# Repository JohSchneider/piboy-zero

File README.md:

# Pi-Boy Zero
aka "PiGrrl-Zero"

[hackaday.io project](https://hackaday.io/project/9467-pigrrl-zero)

*yet another portable console! ;-)*

roughly the size of a gameboy micro, with a 2.2" display

this repository holds:
- the pcb-schematics (kicad)
- stl files for a 3d printable case
- and various setup scripts/tools/config-files to get emulationstation running on this particular hardware setup

## the progress so far

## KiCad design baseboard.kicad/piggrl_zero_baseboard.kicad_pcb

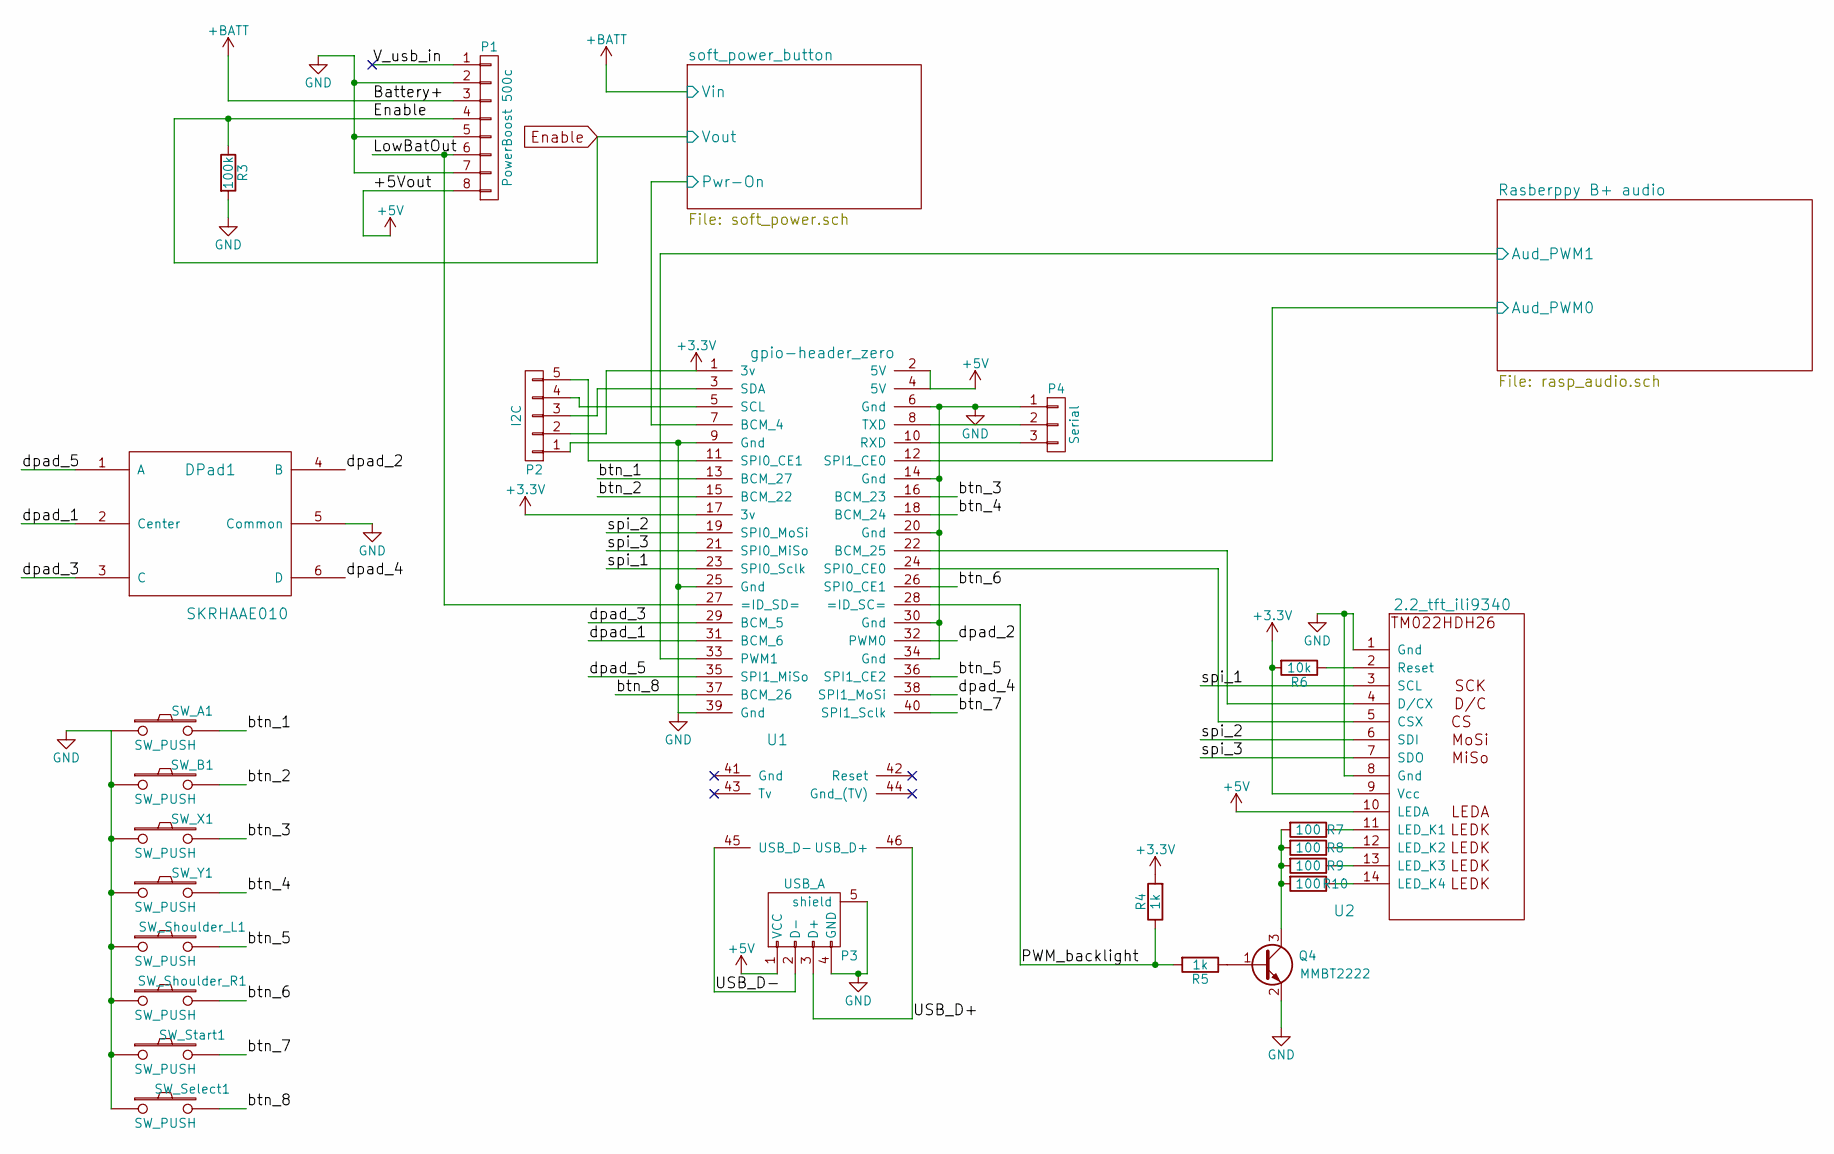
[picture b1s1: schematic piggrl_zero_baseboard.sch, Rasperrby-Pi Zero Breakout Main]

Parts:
DPad1: SKRHAAE010; ManufacturerPartNumber SKRHAAE010
P1: PowerBoost 500c; Powerboost500c
P2: I2C; Pin_Header_Angled_1x05
P3: USB_A
P4: Serial; 1x3_smd_pinheader
Q4: MMBT2222; SOT-23_Handsoldering; ManufacturerPartNumber MMBT2222ALT1G
R3: 100k; R_0805_HandSoldering; ManufacturerPartNumber ERJ-6ENF1003V
R4, R5: 1k; R_0805_HandSoldering; ManufacturerPartNumber ERJ-6ENF1001V
R6: 10k; R_0805_HandSoldering; ManufacturerPartNumber ERJ-6ENF1002V
R7, R8, R9, R10: 100; R_0805_HandSoldering; ManufacturerPartNumber ERJ-6ENF1000V
SW_A1: SW_PUSH; Omron_D2LS_21_woKeyHoles; ManufacturerPartNumber D2LS-21
SW_B1: SW_PUSH; Omron_D2LS_21_woKeyHoles; ManufacturerPartNumber D2LS-21
SW_Select1: SW_PUSH; smd_push_button; ManufacturerPartNumber 2-1437565-8
SW_Shoulder_L1: SW_PUSH; Omron_D2FS_FTN_mirror; ManufacturerPartNumber D2FS-F-N-T
SW_Shoulder_R1: SW_PUSH; Omron_D2FS_FTN; ManufacturerPartNumber D2FS-F-N-T
SW_Start1: SW_PUSH; smd_push_button; ManufacturerPartNumber 2-1437565-8
SW_X1: SW_PUSH; Omron_D2LS_21_woKeyHoles; ManufacturerPartNumber D2LS-21
SW_Y1: SW_PUSH; Omron_D2LS_21_woKeyHoles; ManufacturerPartNumber D2LS-21
U1: gpio-header_zero; raspberry-zero
U2: 2.2_tft_ili9340; TM022HDH26

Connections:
+3V3: P2.2, R4.2, R6.2, U1.1 (3v), U1.17 (3v), U2.9 (Vcc)
+5V: P1.8, P3.1 (VCC), U1.2 (5V), U1.4 (5V), U2.10 (LEDA); also elsewhere on the board
+BATT: P1.3; also elsewhere on the board
/LowBatOut: P1.6, U1.27 (=ID_SD=)
/PWM_backlight: R4.1, R5.2, U1.28 (=ID_SC=)
/Rasberppy B+ audio/Aud_PWM0: U1.12 (SPI1_CE0); also elsewhere on the board
/Rasberppy B+ audio/Aud_PWM1: U1.33 (PWM1); also elsewhere on the board
/USB_D+: P3.3 (D+), U1.46 (USB_D+)
/USB_D-: P3.2 (D-), U1.45 (USB_D-)
/V_usb_in: P1.1
/btn_1: SW_A1.2, U1.13 (BCM_27)
/btn_2: SW_B1.2, U1.15 (BCM_22)
/btn_3: SW_X1.2, U1.16 (BCM_23)
/btn_4: SW_Y1.2, U1.18 (BCM_24)
/btn_5: SW_Shoulder_L1.2, U1.36 (SPI1_CE2)
/btn_6: SW_Shoulder_R1.2, U1.26 (SPI0_CE1)
/btn_7: SW_Start1.2, U1.40 (SPI1_Sclk)
/btn_8: SW_Select1.2, U1.37 (BCM_26)
/dpad_1: DPad1.2 (Center), U1.31 (BCM_6)
/dpad_2: DPad1.4 (B), U1.32 (PWM0)
/dpad_3: DPad1.3 (C), U1.29 (BCM_5)
/dpad_4: DPad1.6 (D), U1.38 (SPI1_MoSi)
/dpad_5: DPad1.1 (A), U1.35 (SPI1_MiSo)
/soft_power_button/Pwr-On: U1.7 (BCM_4); also elsewhere on the board
/spi_1: U1.23 (SPI0_Sclk), U2.3 (SCL)
/spi_2: U1.19 (SPI0_MoSi), U2.6 (SDI)
/spi_3: U1.21 (SPI0_MiSo), U2.7 (SDO)
Enable: P1.4, R3.1; also elsewhere on the board
GND: DPad1.5 (Common), P1.2, P1.5, P1.7, P2.1, P3.4 (GND), P3.5 (shield), P4.1, Q4.2 (E), R3.2, SW_A1.1, SW_B1.1, SW_Select1.1, SW_Shoulder_L1.1, SW_Shoulder_R1.1, SW_Start1.1, SW_X1.1, SW_Y1.1, U1.6 (Gnd), U1.9 (Gnd), U1.14 (Gnd), U1.20 (Gnd), U1.25 (Gnd), U1.30 (Gnd), U1.34 (Gnd), U1.39 (Gnd), U2.1 (Gnd), U2.8 (Gnd); also elsewhere on the board
unnamed: P2.3, U1.3 (SDA)
unnamed: P2.4, U1.5 (SCL)
unnamed: P2.5, U1.11 (SPI0_CE1)
unnamed: P4.2, U1.8 (TXD)
unnamed: P4.3, U1.10 (RXD)
unnamed: Q4.1 (B), R5.1
unnamed: Q4.3 (C), R7.2, R8.2, R9.2, R10.2
unnamed: R6.1, U2.2 (Reset)
unnamed: R7.1, U2.11 (LED_K1)
unnamed: R8.1, U2.12 (LED_K2)
unnamed: R9.1, U2.13 (LED_K3)
unnamed: R10.1, U2.14 (LED_K4)
unnamed: U1.22 (BCM_25), U2.4 (D/CX)
unnamed: U1.24 (SPI0_CE0), U2.5 (CSX)

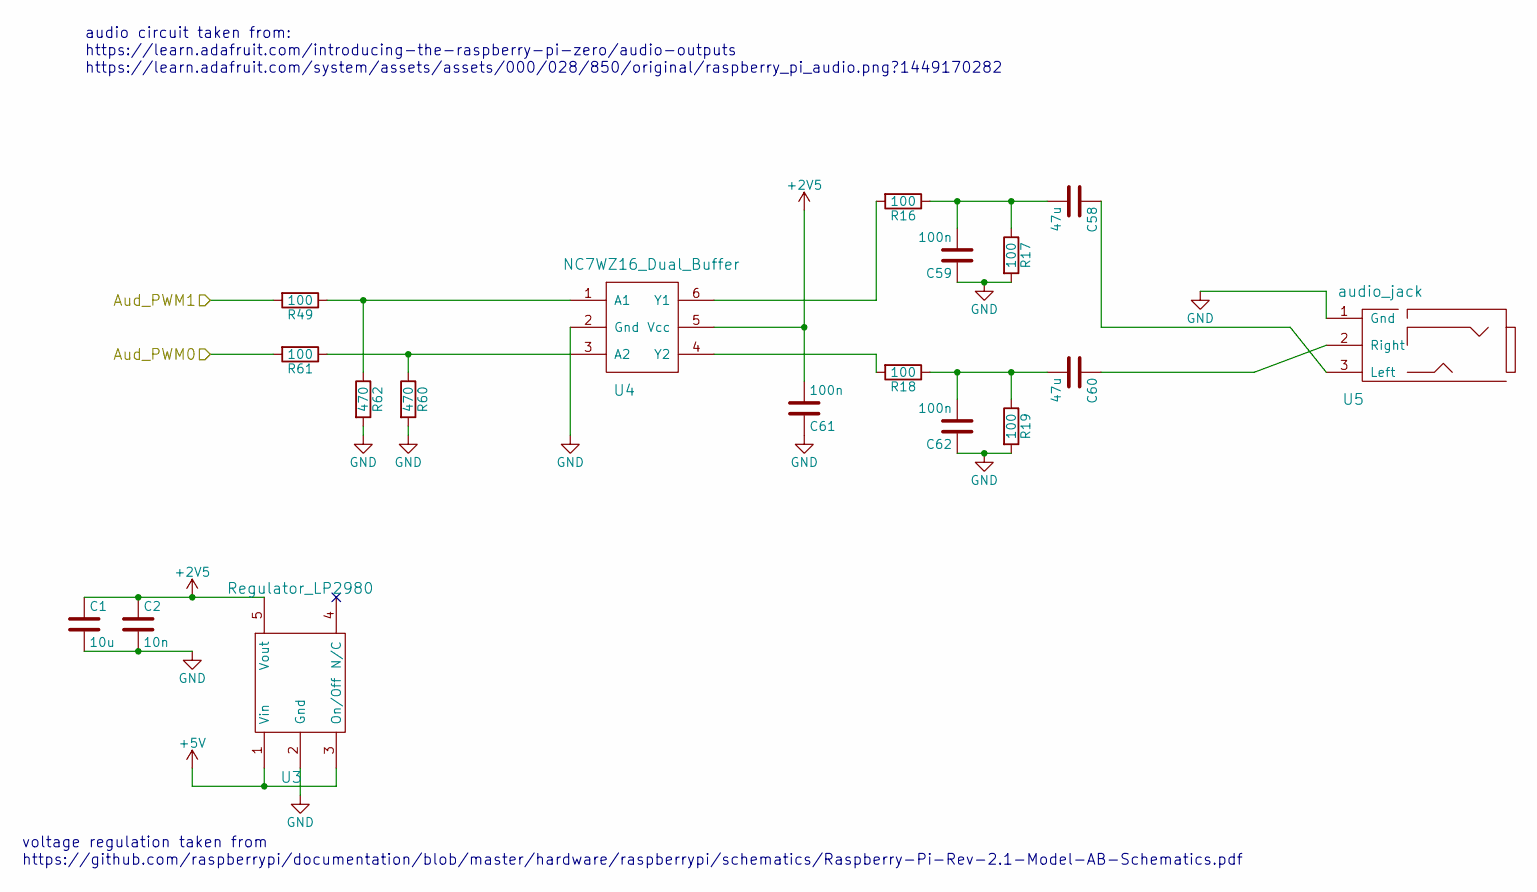
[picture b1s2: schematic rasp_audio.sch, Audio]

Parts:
C1: 10u; C_0805_HandSoldering; ManufacturerPartNumber VJ0805G106KXQTW1BC
C2: 10n; C_0805_HandSoldering; ManufacturerPartNumber VJ0805Y103JXQCW1BC
C58, C60: 47u; C_0805_HandSoldering; ManufacturerPartNumber VJ0805V475MXQTW1BC
C59, C61, C62: 100n; C_0805_HandSoldering; ManufacturerPartNumber VJ0805V104ZXQCW1BC
R16, R17, R18, R19, R49, R61: 100; R_0805_HandSoldering; ManufacturerPartNumber ERJ-6ENF1000V
R60, R62: 470; R_0805_HandSoldering; ManufacturerPartNumber ERJ-6ENF4700V
U3: Regulator_LP2980; SOT-23-5; ManufacturerPartNumber LP2980AIM5-2.5/NOPB
U4: NC7WZ16_Dual_Buffer; SC-70-6_Handsoldering; ManufacturerPartNumber NC7WZ16P6X
U5: audio_jack; audio_smd_SJ-3523-SMT-TR; ManufacturerPartNumber SJ-3523-SMT-TR

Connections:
+2V5: C1.1, C2.1, C61.2, U3.5 (Vout), U4.5 (Vcc)
+5V: U3.1 (Vin), U3.3 (On/Off); also elsewhere on the board
/Rasberppy B+ audio/Aud_PWM0: R61.2; also elsewhere on the board
/Rasberppy B+ audio/Aud_PWM1: R49.2; also elsewhere on the board
GND: C1.2, C2.2, C59.1, C61.1, C62.1, R17.2, R19.2, R60.2, R62.2, U3.2 (Gnd), U4.2 (Gnd), U5.1 (Gnd); also elsewhere on the board
unnamed: C58.1, U5.3 (Left)
unnamed: C58.2, C59.2, R16.1, R17.1
unnamed: C60.1, U5.2 (Right)
unnamed: C60.2, C62.2, R18.1, R19.1
unnamed: R16.2, U4.6 (Y1)
unnamed: R18.2, U4.4 (Y2)
unnamed: R49.1, R62.1, U4.1 (A1)
unnamed: R60.1, R61.1, U4.3 (A2)

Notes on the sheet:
voltage regulation taken from https://github.com/raspberrypi/documentation/blob/master/hardware/raspberrypi/schematics/Raspberry-Pi-Rev-2.1-Model-AB-Schematics.pdf
audio circuit taken from: https://learn.adafruit.com/introducing-the-raspberry-pi-zero/audio-outputs https://learn.adafruit.com/system/assets/assets/000/028/850/original/raspberry_pi_audio.png?1449170282

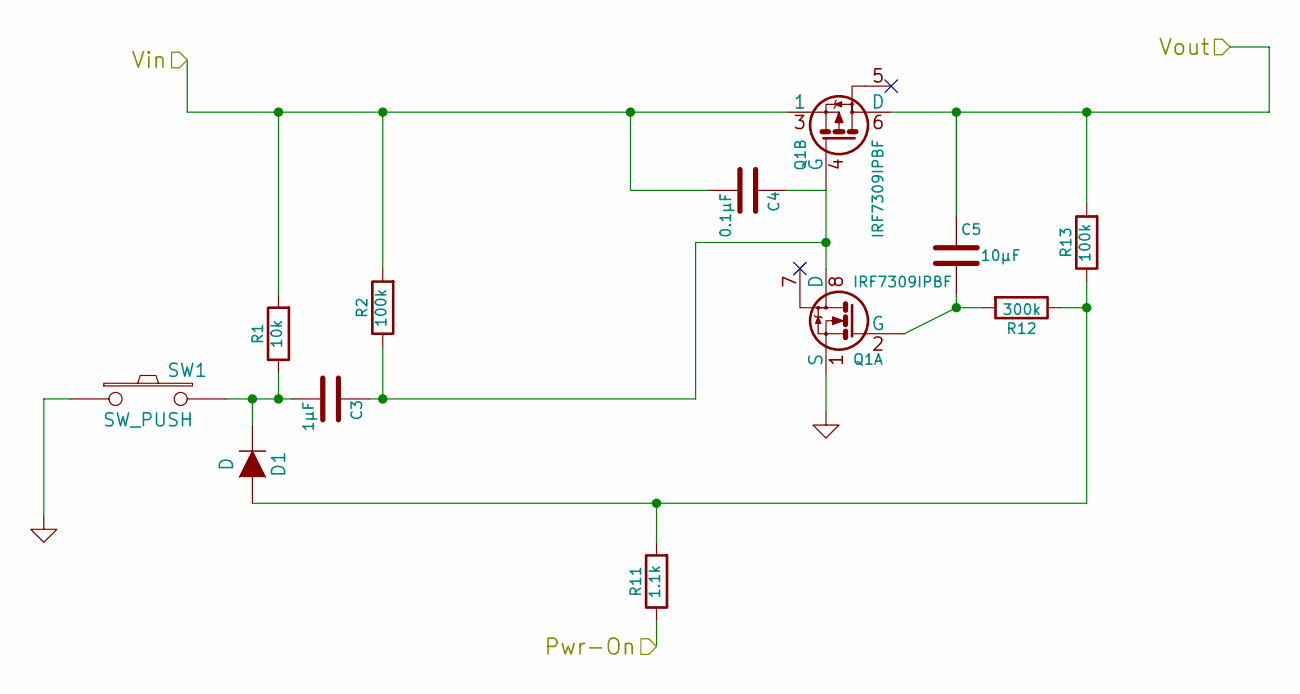
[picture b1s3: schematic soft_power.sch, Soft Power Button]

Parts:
C3: 1µF; C_0805_HandSoldering; ManufacturerPartNumber VJ0805Y105KXQTW1BC
C4: 0.1µF; C_0805_HandSoldering; ManufacturerPartNumber 885012207098
C5: 10µF; C_0805_HandSoldering; ManufacturerPartNumber VJ0805G106KXQTW1BC
D1: D; SOD-123; ManufacturerPartNumber 1N4148W-TP
Q1: IRF7309IPBF; SOIC-8-N; ManufacturerPartNumber IRF7309PBF
R1: 10k; R_0805_HandSoldering; ManufacturerPartNumber ERJ-6ENF1002V
R2, R13: 100k; R_0805_HandSoldering; ManufacturerPartNumber ERJ-6ENF1003V
R11: 1.1k; R_0805_HandSoldering; ManufacturerPartNumber ERJ-6ENF1101V
R12: 300k; R_0805_HandSoldering; ManufacturerPartNumber ERJ-6ENF3003V
SW1: SW_PUSH; btn_1571262-1; ManufacturerPartNumber 1571262-1

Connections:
+BATT: C4.2, Q1.3 (1), R1.2, R2.2; also elsewhere on the board
/soft_power_button/Pwr-On: R11.1; also elsewhere on the board
Enable: C5.2, Q1.6 (D), R13.2; also elsewhere on the board
GND: Q1.1 (S), SW1.1; also elsewhere on the board
unnamed: C3.1, C4.1, Q1.4 (G), Q1.8 (D), R2.1
unnamed: C3.2, D1.1 (K), R1.1, SW1.2
unnamed: C5.1, Q1.2 (G), R12.2
unnamed: D1.2 (A), R11.2, R12.1, R13.1

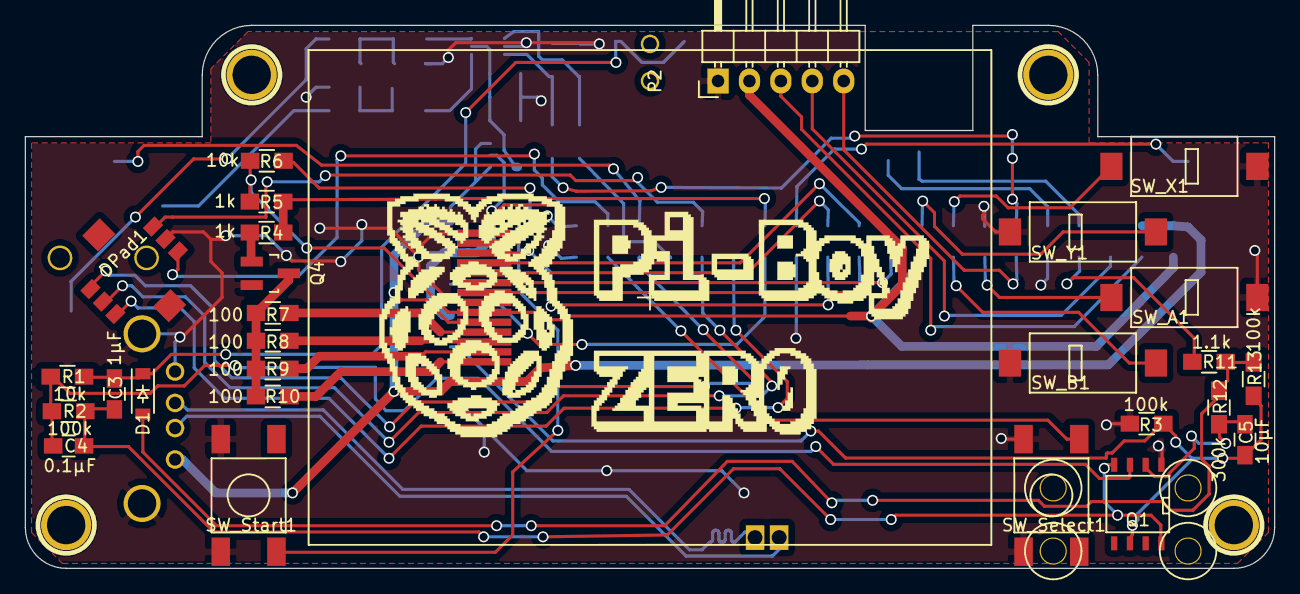
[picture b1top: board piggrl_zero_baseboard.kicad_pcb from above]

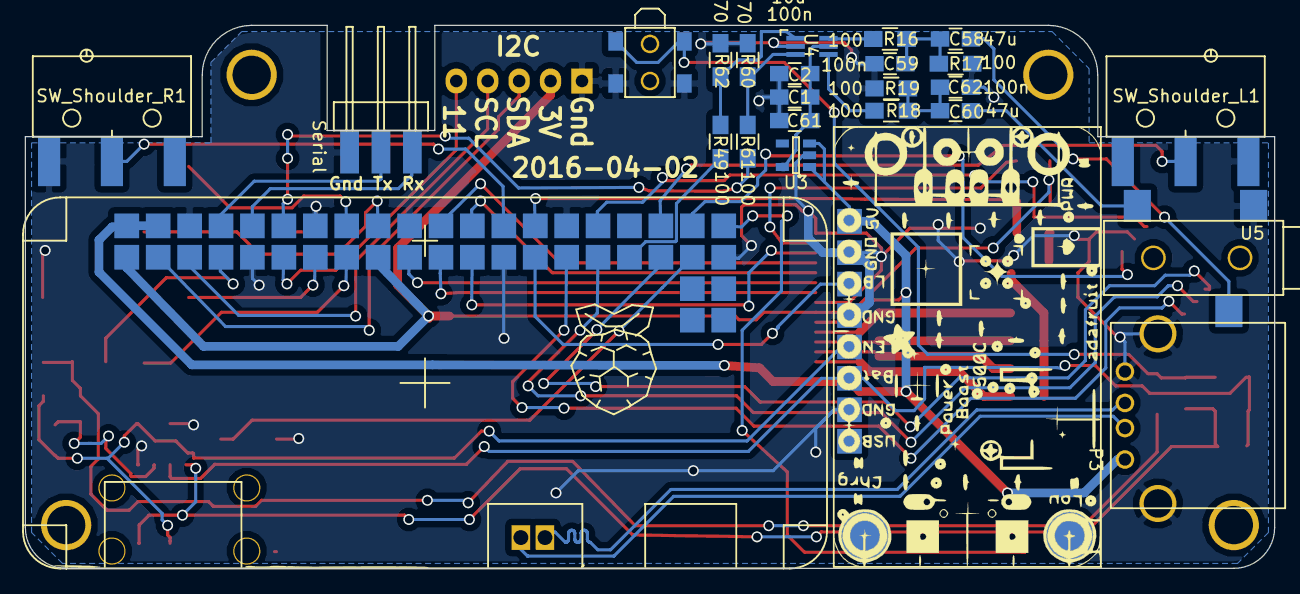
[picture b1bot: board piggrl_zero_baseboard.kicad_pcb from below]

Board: 2 copper layers, 101.0 x 43.9 mm, 57 parts (25 on the bottom side), 55 nets.

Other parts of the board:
1PIN, 1PIN#2, 1PIN#3, 1PIN#4: P***; 1pin

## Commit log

2016-02-15 push to github
2016-02-15 added README.md
2016-02-18 added connection from low-bat on the powerboost to the (till now) unused ID_SD pin
    since we already used ID_SC for display-pwm, the whole board won't turn into an spec-compliant hat anyway...
2016-02-18 added initial rough design sketches
2016-02-26 added (initial?) license
2016-03-03 fixed switched Value/Reference in soft_power schematic (showed in bad BOM references)
2016-03-04 cleanup of silkscreen for better readability during assembly
    generated and pushed new boardfiles to oshpark
2016-03-05 added solder&test area highlight images
2016-03-05 fixed wrong transistor pinout on softpower p-mosfet
    common pinout is GSD and not DSG!
2016-03-07 fixed mounting hole diameter which was slightly too small for an M3 screw
2016-03-07 fixed position of solder-holes to the usb-test-pads on the pi-zero
2016-03-07 added through-hole pads as clearance for the hdmi-connectors tabs on the raspberry-zero
    and rerouted some traces to make way
2016-03-07 added net_name to usb data lines and rerouted them on the pcb
    one less via, and usign kicads wonderfull differential-pair routing tool :-)
2016-03-10 bugfix: backlicht transistor pinout was BCE instead of common BEC
2016-03-10 ditch mosfet as softpower inverter and use same BJT transistor as the one used for the backlight
2016-03-10 turns out we don't need the transistor (Q3) at all... so remove it, leaving only the 100k pulldown on the powerboosts enable pin
2016-03-10 cleanup some traces
    and restore the accidentally deleted raspberry-footprint :-p
2016-03-11 replottet pcb that was fabbed, since plot of front copper layer was broken
    plottet version at 96a7204d41cedd91349ca2518c14b511f5b00693
2016-03-11 small script to do a visual diff on kicads pcb printouts (pdf)
2016-03-13 added 3d model of the pi-zero - based on caliper measurements
2016-03-13 corrected usb-pad positions and mini-hdmi-tabs cutout based on 3d model
2016-03-13 added more 3d models
2016-03-13 added a nice 8bit-ish logo to the front silkscreen :-)
    ... that will be covered by the screen :'-(
2016-03-13 documented errors in revision 2016-02-13 and generated current board revision 2016-03-13 that has them fixed
2016-03-13 added pcb rendering in perfect-purple '#800080' and the gimp-file for the new front image
2016-03-14 added BOM for snapshot 2016-03-13
2016-04-02 snapshot of upstream Retrogame
    https://github.com/adafruit/Adafruit-Retrogame rev: 4d59757aa820dcf8ff90dd155ed8119bbb082b89
2016-04-02 fixed start/select button footprint
    commonly those push buttons pair their four pins the other way...
2016-04-03 added fb-cp, which will be used to mirror the hdmi output to the pitft
    origin:
    https://github.com/tasanakorn/rpi-fbcp
    revision:
    8087a71d0330a078d91aa78656684ab5313616c6
2016-04-09 adapt adafruits retrogame to our needs
    and add init.d daemon file to start it during boot
2016-04-09 added init.d daemon file for fbcp
2016-04-09 added manifest/references to the software sources
2016-04-09 initial version of the retropie sd-card setup script
2016-04-09 added pwm-audio devicetree-overlays
2016-04-09 added 3dprintable case
2016-04-11 updated readme and some other stuff :P
2016-04-11 added print/build instructions
2016-05-12 added udev rule for retrogame
    for gpio-buttons to work with libretro retrogame needs to be configured by udev properly
2017-01-18 Fixed an update-rc shortcut command issue. Added a small readme to explain the gist of the software setup
2017-02-09 systemd service for fbcp
2017-02-09 xorg config for cursor-mouse
2017-02-09 button overlay
2017-02-09 python powerbutton + systemd service-file
2017-02-09 added lokal fork of pi-blaster
    original version from:
    https://github.com/sarfata/pi-blaster.git
    revision:
    ec5e1b4c6191d8f9a538497dbbb86f9cf0de7016
    used to control the display backlight, will be modified for that
2017-02-09 modifications to pi-blaster for piboy tft backlight control
2017-02-09 more init.d stuff, not used in recent retropi though...
2017-02-09 remove unused stuff on current os (retropie 4.1)
2017-02-09 added pitft22 dtb used by the display
    seems not to be part of recent upstream overlay collection anymore...
2017-02-09 pi-blaster: replaced local fork with submodule of upstream repository
2017-02-09 pi-blaster config, to be put in /etc/default/pi-blaster
    with settings for the display backlight PWM control
2017-02-09 added install steps of pi-blaster to setup-script
2017-02-09 install custom boot-splash-screen :-)
2017-02-10 update setup script
2017-02-10 emulation-station configuration for the piboy-zero (including retrogame input setting)
2017-02-10 added utility menu entries in emulationstations 'retropie' menu
